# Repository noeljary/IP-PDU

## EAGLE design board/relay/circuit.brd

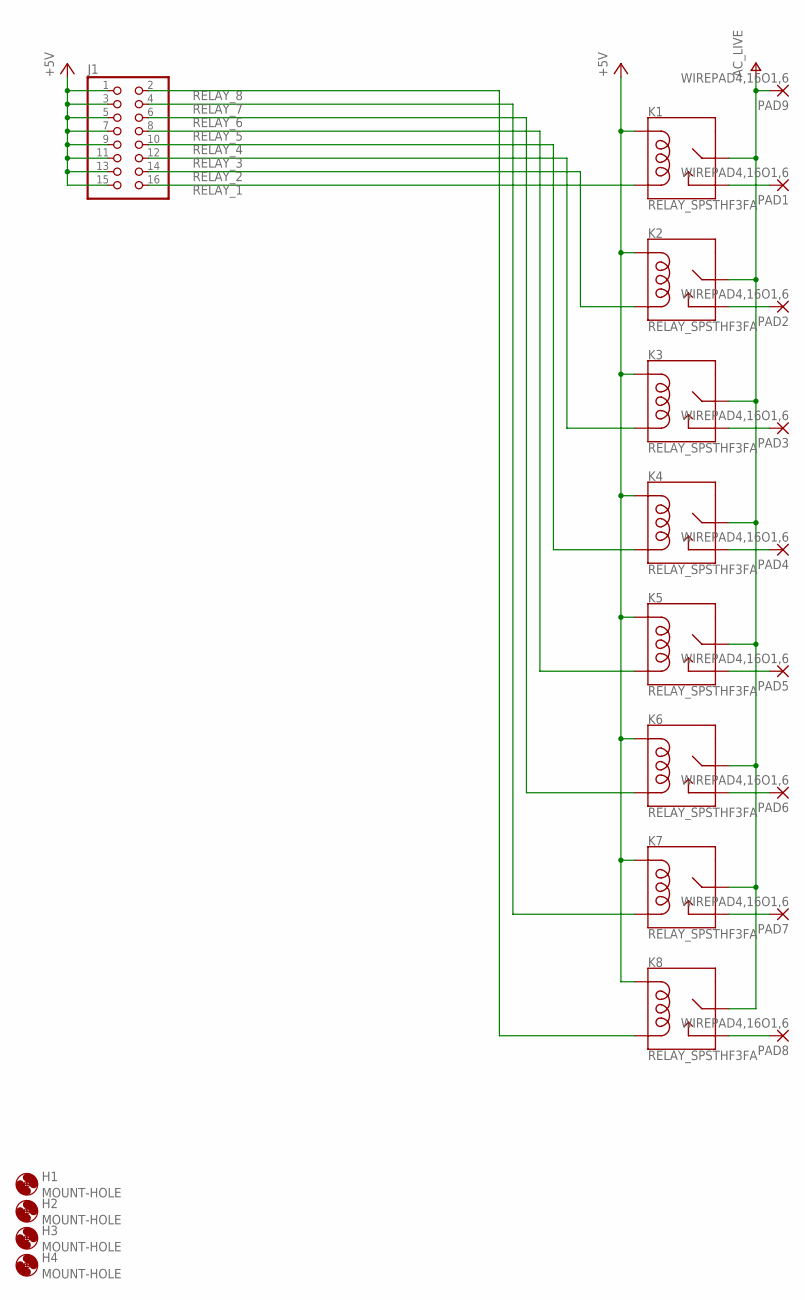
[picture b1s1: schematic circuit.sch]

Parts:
H1, H2, H3, H4: MOUNT-HOLE; 3,2
J1: LED; 2X08
K1, K2, K3, K4, K5, K6, K7, K8: RELAY_SPSTHF3FA; RELAY_HF3FA
PAD1, PAD2, PAD3, PAD4, PAD5, PAD6, PAD7, PAD8, PAD9: WIREPAD4,16O1,6; 4,16O1,6

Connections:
+5V: J1.1, J1.3, J1.5, J1.7, J1.9, J1.11, J1.13, J1.15, K1.P$1 (COIL1), K2.P$1 (COIL1), K3.P$1 (COIL1), K4.P$1 (COIL1), K5.P$1 (COIL1), K6.P$1 (COIL1), K7.P$1 (COIL1), K8.P$1 (COIL1)
unnamed: K8.P$3 (NO), PAD8.1
unnamed: K7.P$3 (NO), PAD7.1
unnamed: K6.P$3 (NO), PAD6.1
unnamed: K5.P$3 (NO), PAD5.1
unnamed: K4.P$3 (NO), PAD4.1
unnamed: K3.P$3 (NO), PAD3.1
unnamed: K2.P$3 (NO), PAD2.1
unnamed: K1.P$3 (NO), PAD1.1
RELAY_1: J1.16, K1.P$2 (COIL2)
RELAY_2: J1.14, K2.P$2 (COIL2)
RELAY_3: J1.12, K3.P$2 (COIL2)
RELAY_4: J1.10, K4.P$2 (COIL2)
RELAY_5: J1.8, K5.P$2 (COIL2)
RELAY_6: J1.6, K6.P$2 (COIL2)
RELAY_7: J1.4, K7.P$2 (COIL2)
RELAY_8: J1.2, K8.P$2 (COIL2)
V+: K1.P$4 (MAIN), K2.P$4 (MAIN), K3.P$4 (MAIN), K4.P$4 (MAIN), K5.P$4 (MAIN), K6.P$4 (MAIN), K7.P$4 (MAIN), K8.P$4 (MAIN), PAD9.1

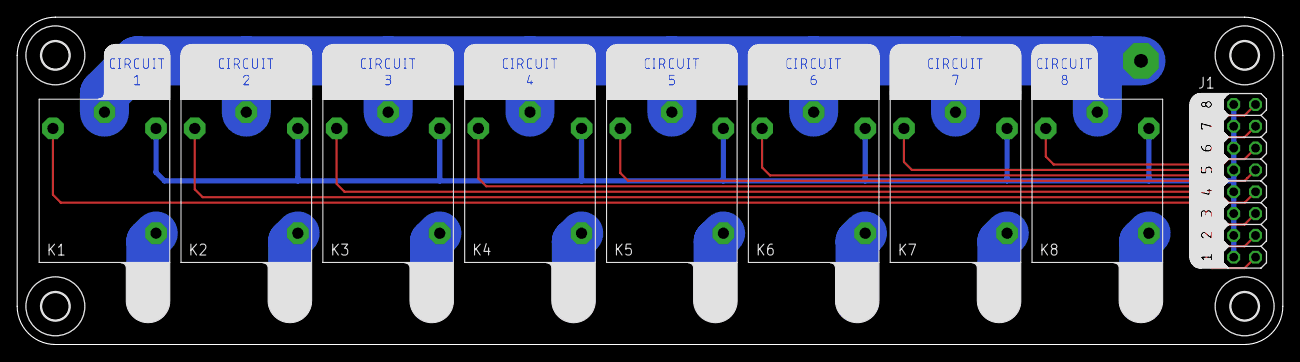
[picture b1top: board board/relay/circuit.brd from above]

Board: 2 copper layers, 147.3 x 38.1 mm, 22 parts (0 on the bottom side), 18 nets.

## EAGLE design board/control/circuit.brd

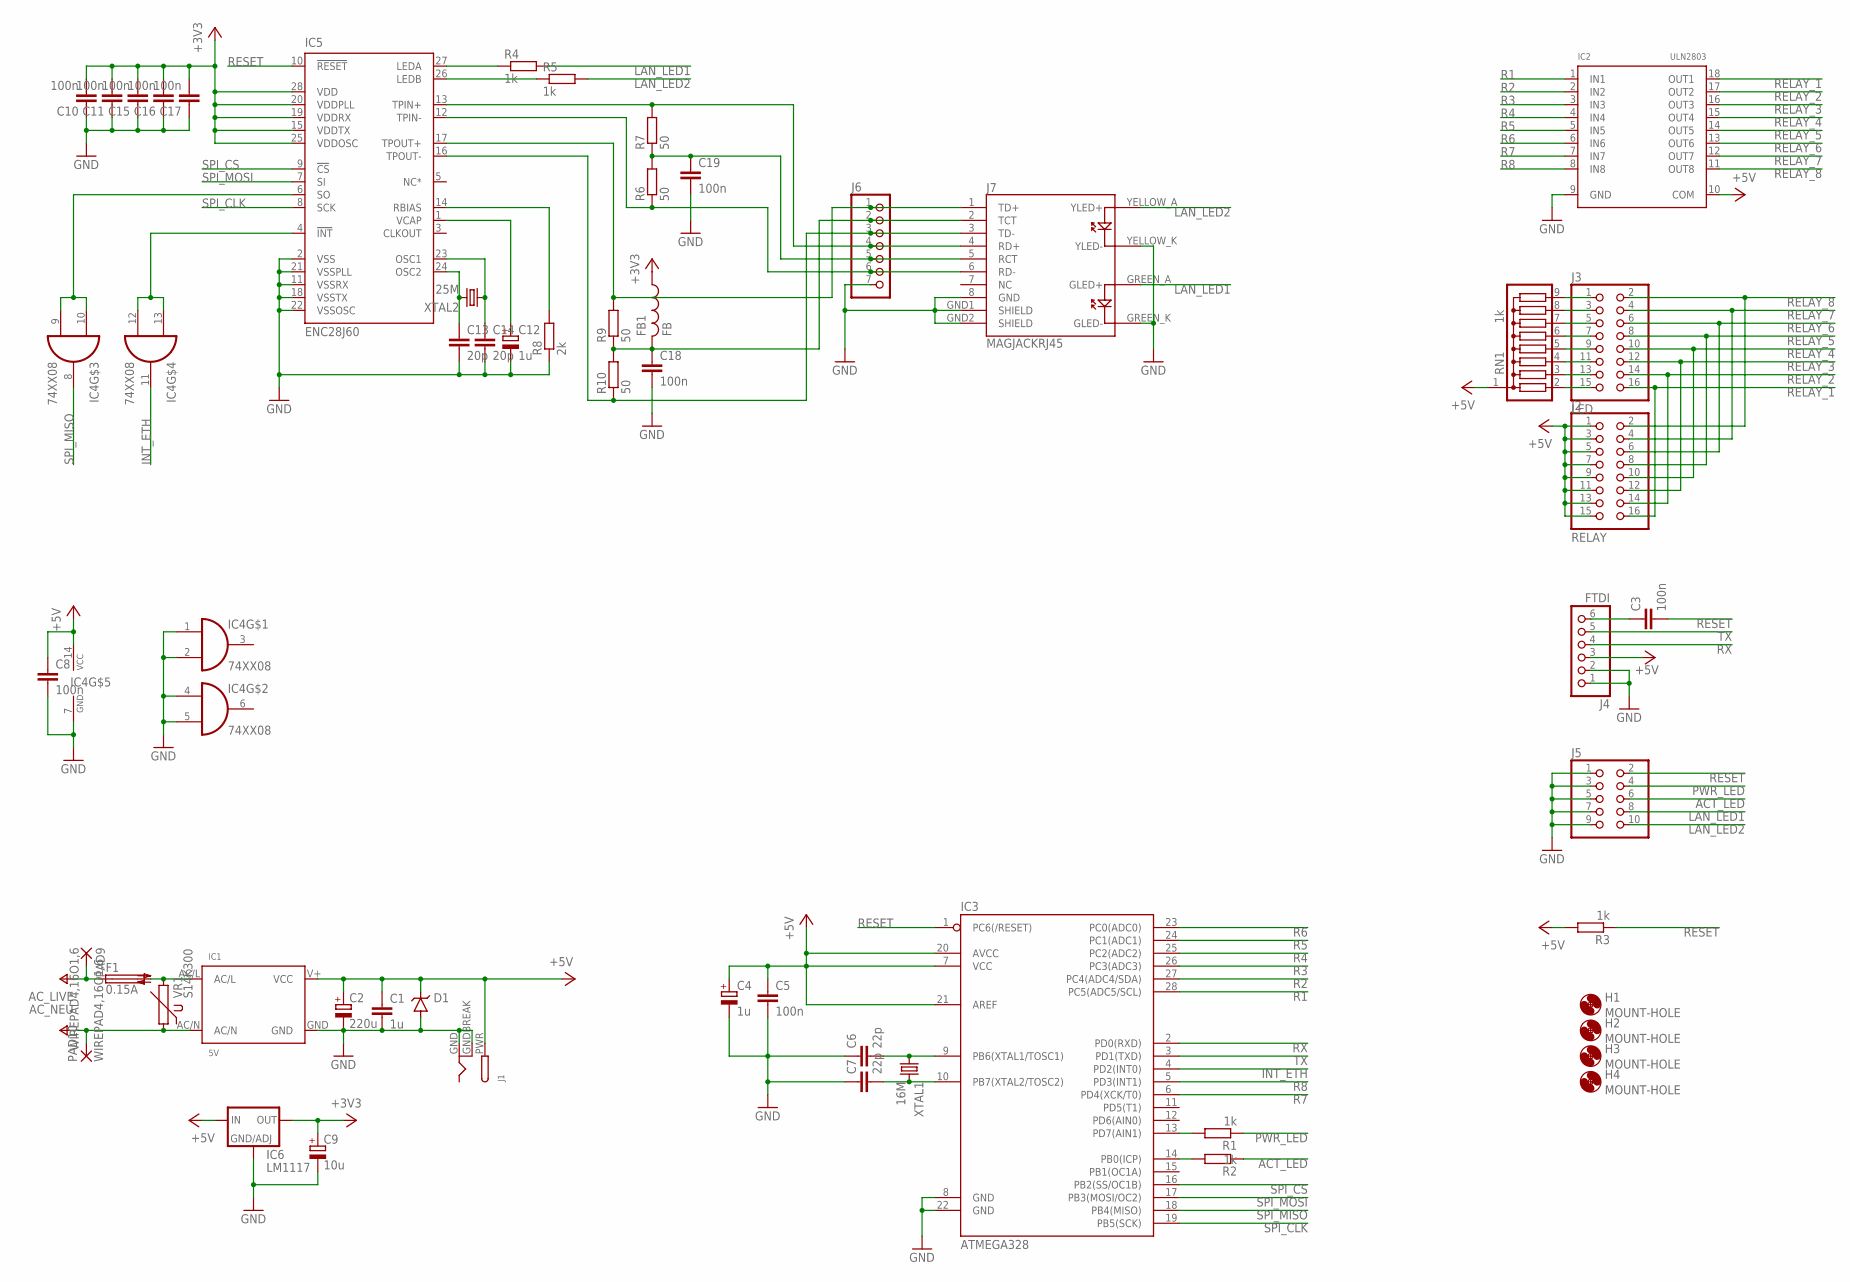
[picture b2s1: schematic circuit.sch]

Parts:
C1: 1u; C050-025X075
C2: 220u; E2,5-6
C3, C5, C8, C10, C11, C15, C16, C17, C18, C19: 100n; C050-025X075
C4, C12: 1u; E5-5
C6, C7: 22p; C025-025X050
C9: 10u; E5-5
C13, C14: 20p; C025-025X050
D1: DIODE-TVSDO15; DO15
F1: 0.15A; 5X20_FUSE
FB1: FB
H1, H2, H3, H4: MOUNT-HOLE; 3,2
IC1: 5V; LD/AMEL10
IC2: ULN2803; DIL18
IC3: ATMEGA328; DIL28
IC4: 74XX08; DIL14
IC5: ENC28J60; DIL28
IC6: LM1117; TO220V
J1: DCBARRELPTH; DCJACK_2MM_PTH
J2: RELAY; 2X08
J3: LED; 2X08
J4: FTDI; 1X06
J5: PINHD-2X5; 2X05
J6: PINHD-1X7; 1X07
J7: MAGJACKRJ45; MAGJACK
PAD9, PAD10: WIREPAD4,16O1,6; 4,16O1,6
R1, R2, R3, R4, R5: 1k; 0207/10
R6, R7, R9, R10: 50; 0207/10
R8: 2k; 0207/10
RN1: 1k; SIL9
VR1: S14K300
XTAL1: 16M; HC49/S
XTAL2: 25M; HC49/S

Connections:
+3V3: C9.+, C10.2, C11.2, C15.2, C16.2, C17.2, FB1.P$1 (1), IC5.15 (VDDTX), IC5.19 (VDDRX), IC5.20 (VDDPLL), IC5.25 (VDDOSC), IC5.28 (VDD), IC6.2 (OUT)
+5V: C1.1, C2.+, C4.+, C5.1, C8.1, D1.C, IC1.V+ (VCC), IC2.10 (COM), IC3.7 (VCC), IC3.20 (AVCC), IC3.21 (AREF), IC4.14 (VCC), IC6.3 (IN), J1.PWR, J2.1, J2.3, J2.5, J2.7, J2.9, J2.11, J2.13, J2.15, J4.3, R3.2, RN1.1
ACT_LED: J5.6, R2.1
GND: C1.2, C2.-, C4.-, C5.2, C6.1, C7.1, C8.2, C9.-, C10.1, C11.1, C12.-, C13.2, C14.2, C15.1, C16.1, C17.1, C18.2, C19.2, D1.A, IC1.GND, IC2.9 (GND), IC3.8 (GND), IC3.22 (GND), IC4.1 (I0), IC4.2 (I1), IC4.4 (I0), IC4.5 (I1), IC4.7 (GND), IC5.2 (VSS), IC5.11 (VSSRX), IC5.18 (VSSTX), IC5.21 (VSSPLL), IC5.22 (VSSOSC), IC6.1 (GND/ADJ), J1.GND, J1.GNDBREAK, J4.1, J4.2, J5.1, J5.3, J5.5, J5.7, J5.9, J6.7, J7.8 (GND), J7.GND1 (SHIELD), J7.GND2 (SHIELD), J7.GREEN_K (GLED-), J7.YELLOW_K (YLED-), R8.1
INT_ETH: IC3.4 (PD2(INT0)), IC4.11 (O)
LAN_LED1: J5.8, J7.GREEN_A (GLED+), R4.2
LAN_LED2: J5.10, J7.YELLOW_A (YLED+), R5.2
unnamed: IC5.16 (TPOUT-), J6.3, J7.3 (TD-), R10.1
unnamed: C19.1, J6.5, J7.5 (RCT), R6.2, R7.1
unnamed: IC5.17 (TPOUT+), J6.1, J7.1 (TD+), R9.2
unnamed: J3.15, RN1.2
unnamed: J3.13, RN1.3
unnamed: F1.2A (2), F1.2B (2), IC1.AC/L, VR1.2
unnamed: IC4.9 (I1), IC4.10 (I0), IC5.6 (SO)
unnamed: J3.11, RN1.4
unnamed: IC4.12 (I1), IC4.13 (I0), IC5.4 (!INT)
unnamed: J3.9, RN1.5
unnamed: J3.7, RN1.6
unnamed: J3.5, RN1.7
unnamed: J3.3, RN1.8
unnamed: C18.1, FB1.P$2 (2), J6.2, J7.2 (TCT), R9.1, R10.2
unnamed: IC5.13 (TPIN+), J6.4, J7.4 (RD+), R7.2
unnamed: IC5.12 (TPIN-), J6.6, J7.6 (RD-), R6.1
unnamed: IC5.27 (LEDA), R4.1
unnamed: IC5.26 (LEDB), R5.1
unnamed: IC3.13 (PD7(AIN1)), R1.2
unnamed: IC3.14 (PB0(ICP)), R2.2
unnamed: J3.1, RN1.9
unnamed: C3.1, J4.6
unnamed: C13.1, IC5.24 (OSC2), XTAL2.2
unnamed: C14.1, IC5.23 (OSC1), XTAL2.1
unnamed: C12.+, IC5.1 (VCAP)
unnamed: IC5.14 (RBIAS), R8.2
unnamed: C6.2, IC3.9 (PB6(XTAL1/TOSC1)), XTAL1.1
unnamed: C7.2, IC3.10 (PB7(XTAL2/TOSC2)), XTAL1.2
PWR_LED: J5.4, R1.1
R1: IC2.1 (IN1), IC3.28 (PC5(ADC5/SCL))
R2: IC2.2 (IN2), IC3.27 (PC4(ADC4/SDA))
R3: IC2.3 (IN3), IC3.26 (PC3(ADC3))
R4: IC2.4 (IN4), IC3.25 (PC2(ADC2))
R5: IC2.5 (IN5), IC3.24 (PC1(ADC1))
R6: IC2.6 (IN6), IC3.23 (PC0(ADC0))
R7: IC2.7 (IN7), IC3.6 (PD4(XCK/T0))
R8: IC2.8 (IN8), IC3.5 (PD3(INT1))
RELAY_1: IC2.18 (OUT1), J2.16, J3.16
RELAY_2: IC2.17 (OUT2), J2.14, J3.14
RELAY_3: IC2.16 (OUT3), J2.12, J3.12
RELAY_4: IC2.15 (OUT4), J2.10, J3.10
RELAY_5: IC2.14 (OUT5), J2.8, J3.8
RELAY_6: IC2.13 (OUT6), J2.6, J3.6
RELAY_7: IC2.12 (OUT7), J2.4, J3.4
RELAY_8: IC2.11 (OUT8), J2.2, J3.2
RESET: C3.2, IC3.1 (PC6(/RESET)), IC5.10 (!RESET), J5.2, R3.1
RX: IC3.2 (PD0(RXD)), J4.4
SPI_CLK: IC3.19 (PB5(SCK)), IC5.8 (SCK)
SPI_CS: IC3.16 (PB2(SS/OC1B)), IC5.9 (!CS)
SPI_MISO: IC3.18 (PB4(MISO)), IC4.8 (O)
SPI_MOSI: IC3.17 (PB3(MOSI/OC2)), IC5.7 (SI)
TX: IC3.3 (PD1(TXD)), J4.5
V+: F1.1A (1), F1.1B (1), PAD9.1
V-: IC1.AC/N, PAD10.1, VR1.1

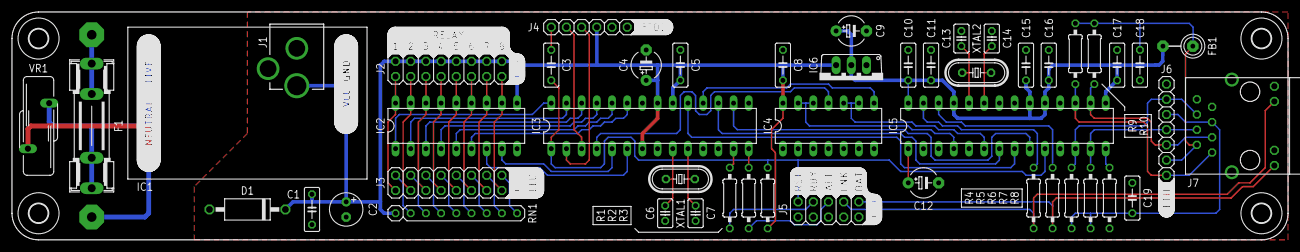
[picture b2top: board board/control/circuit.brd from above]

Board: 2 copper layers, 213.4 x 38.1 mm, 55 parts (0 on the bottom side), 61 nets.

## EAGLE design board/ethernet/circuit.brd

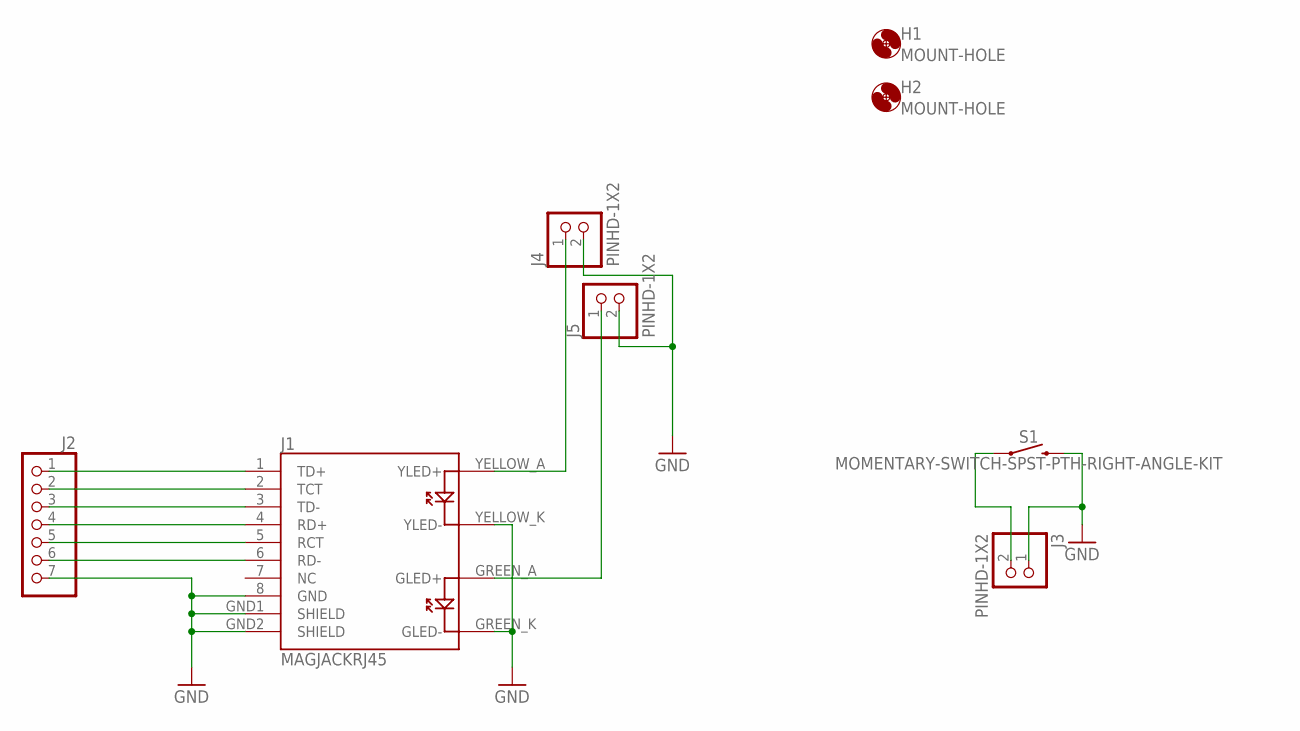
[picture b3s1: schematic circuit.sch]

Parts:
H1, H2: MOUNT-HOLE; 3,2
J1: MAGJACKRJ45; MAGJACK
J2: PINHD-1X7; 1X07
J3, J4, J5: PINHD-1X2; 1X02
S1: MOMENTARY-SWITCH-SPST-PTH-RIGHT-ANGLE-KIT; TACTILE_SWITCH_PTH_RIGHT_ANGLE_KIT

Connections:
GND: J1.8 (GND), J1.GND1 (SHIELD), J1.GND2 (SHIELD), J1.GREEN_K (GLED-), J1.YELLOW_K (YLED-), J2.7, J3.1, J4.2, J5.2, S1.2
unnamed: J1.1 (TD+), J2.1
unnamed: J1.2 (TCT), J2.2
unnamed: J1.3 (TD-), J2.3
unnamed: J1.4 (RD+), J2.4
unnamed: J1.5 (RCT), J2.5
unnamed: J1.6 (RD-), J2.6
unnamed: J1.YELLOW_A (YLED+), J4.1
unnamed: J1.GREEN_A (GLED+), J5.1
unnamed: J3.2, S1.1

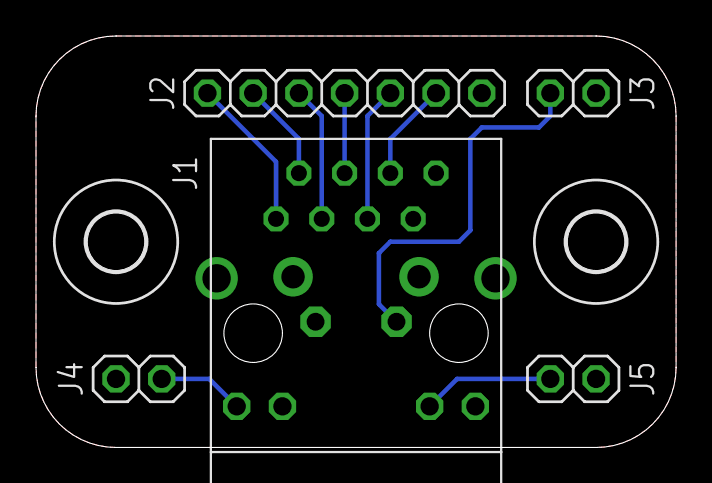
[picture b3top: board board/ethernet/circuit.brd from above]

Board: 2 copper layers, 35.6 x 22.9 mm, 8 parts (1 on the bottom side), 10 nets.

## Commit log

2022-12-03 Adding IP PDU project into version control
